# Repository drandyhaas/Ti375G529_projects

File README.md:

# Ti375G529_projects

Test projects for the Efinix Ti375C529 development kit with LPDDR4x memory and FT60X USB3 interface.

## Setup

Make sure to use Zadig to choose the libusb-win32 driver for the Ti dev board interfaces 0 and 1, then it will show up in the programmer.

## Projects

| Directory | Description |
|-----------|-------------|
| [Blink](Blink/) | Simple LED blink example - basic FPGA sanity test |
| [FT601_loopback](FT601_loopback/) | FT60X USB3 loopback test - verify USB communication |
| [LPDDR4](LPDDR4/) | DDR memory test with hardware auto-init and 74+ Gb/s bandwidth verification |
| [LVDS_LPDDR4](LVDS_LPDDR4/) | Digital scope with LVDS inputs, DDR buffering, USB3 readback (Ti375C529) |
| [ti_lpddr4_debug_tools](ti_lpddr4_debug_tools/) | Python tools for DDR calibration and debugging via JTAG |

## Project Details

### [Blink](Blink/)
Minimal LED blink project for verifying FPGA programming and basic I/O.

### [FT601_loopback](FT601_loopback/)
USB3 FT60X interface test. Requires FT60X drivers (v1.3.0.10 recommended) and configuration to 1-channel 245 FIFO mode.

### [LPDDR4](LPDDR4/)
LPDDR4x memory controller test system:
- Hardware auto-initialization on power-up
- LFSR-based memory test with 100% data verification
- 74.36 Gb/s bandwidth (93% efficiency)
- USB3 control interface

### [LVDS_LPDDR4](LVDS_LPDDR4/)
High-speed data acquisition system for Ti375C529:
- 4-channel 10-bit LVDS input at 750 MHz
- LPDDR4 waveform buffer (81+ Gb/s)
- Configurable triggering and downsampling
- USB3 readout (~280 MB/s)
- Command processor with 8-byte protocol

### [ti_lpddr4_debug_tools](ti_lpddr4_debug_tools/)
Python-based DDR debugging and calibration tools:
- JTAG interface for register access
- DDR initialization and training
- Timing scan and calibration
- Gate leveling and read leveling

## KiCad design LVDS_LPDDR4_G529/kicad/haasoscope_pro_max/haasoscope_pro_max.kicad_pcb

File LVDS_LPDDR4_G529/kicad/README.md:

# KiCad Schematic Symbols for Haasoscope Pro Max

This directory contains KiCad schematic symbols and generators for the Haasoscope Pro Max FPGA board.

## Schematic and Board

- [Schematic PDF](haasoscope_pro_max/schematic.pdf)
- [Board Layout](haasoscope_pro_max/board.png)

## Generated Symbols

### Ti90G529_Functions.kicad_sym

Multi-unit FPGA symbol for the Efinix Ti90G529, organized by peripheral interface for easy schematic wiring:

| Unit | Name | Pin Side | Connects To |
|------|------|----------|-------------|
| 1 | FT601 Interface | LEFT | FT601Q USB3 FIFO |
| 2 | ADC 1/2 LVDS Data | RIGHT | ADC12DL500ACF (channels 1-2) |
| 3 | ADC 3/4 LVDS Data | RIGHT | ADC12DL500ACF (channels 3-4) |
| 4 | ADC LVDS Clocks | RIGHT | ADC clock outputs |
| 5 | DDR4 Interface | LEFT (data), RIGHT (control) | MT53D512M16D1DS LPDDR4 |
| 6 | Misc I/O | LEFT (inputs), RIGHT (outputs/SPI) | LEDs, buttons, SPI, etc. |
| 7 | CONFIG/JTAG | LEFT | Programming interface |
| 8 | VCC Power | LEFT and RIGHT | Power supplies |
| 9 | GND | LEFT and RIGHT | Ground |
| 10 | Unassigned GPIO | LEFT | Unused GPIO pins |

### Aligned_Peripheral_Symbols.kicad_sym

Peripheral chip symbols with pins arranged to align with the Ti90G529_Functions symbol:

- **FT601Q_Aligned** - USB3 FIFO, FIFO interface on RIGHT to connect to FPGA on LEFT
- **ADC12DL500ACF_Aligned** - Dual 12-bit ADC, LVDS outputs on LEFT to connect to FPGA on RIGHT
- **MT53D512M16D1DS_Aligned** - LPDDR4 memory, data on RIGHT, control/address on LEFT with gaps for dual-channel wiring

## Symbol Generators

### generate_ti90g529_symbol_with_functions.py

Generates `Ti90G529_Functions.kicad_sym` by parsing the Efinity peri.xml to automatically categorize GPIO pins by their assigned function.

### generate_aligned_peripheral_symbols.py

Generates `Aligned_Peripheral_Symbols.kicad_sym` with pin ordering matched to the FPGA symbol for horizontal wire alignment.

### generate_ti90g529_symbol.py

Base symbol generator with FPGA pin definitions imported by the other generators.

## Original Symbol Sources

- `ADC12DL/` - Original ADC12DL500ACF symbol
- `MT53D512M32D2DS-053 WT_D/` - Original MT53 DDR symbol
- `G529.pretty/` - Footprint library

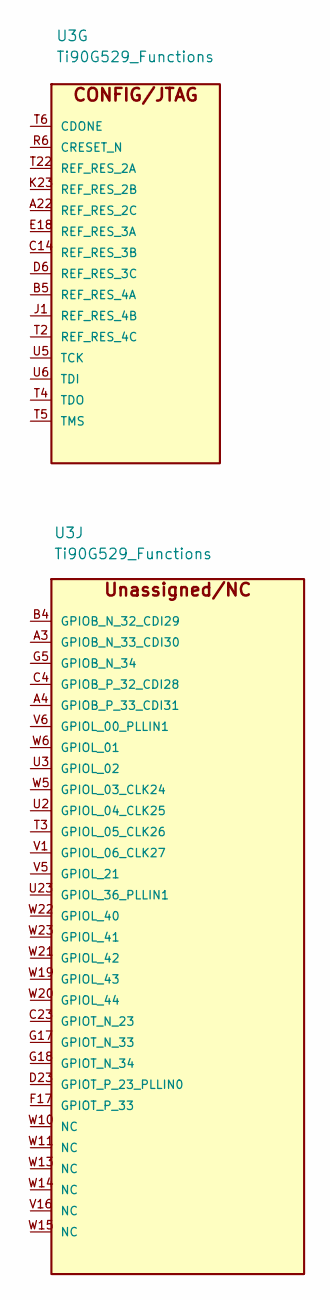
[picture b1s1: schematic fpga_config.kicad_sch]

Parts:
U3: Ti90G529_Functions; BGA-529_23x23_19.0x19.0mm

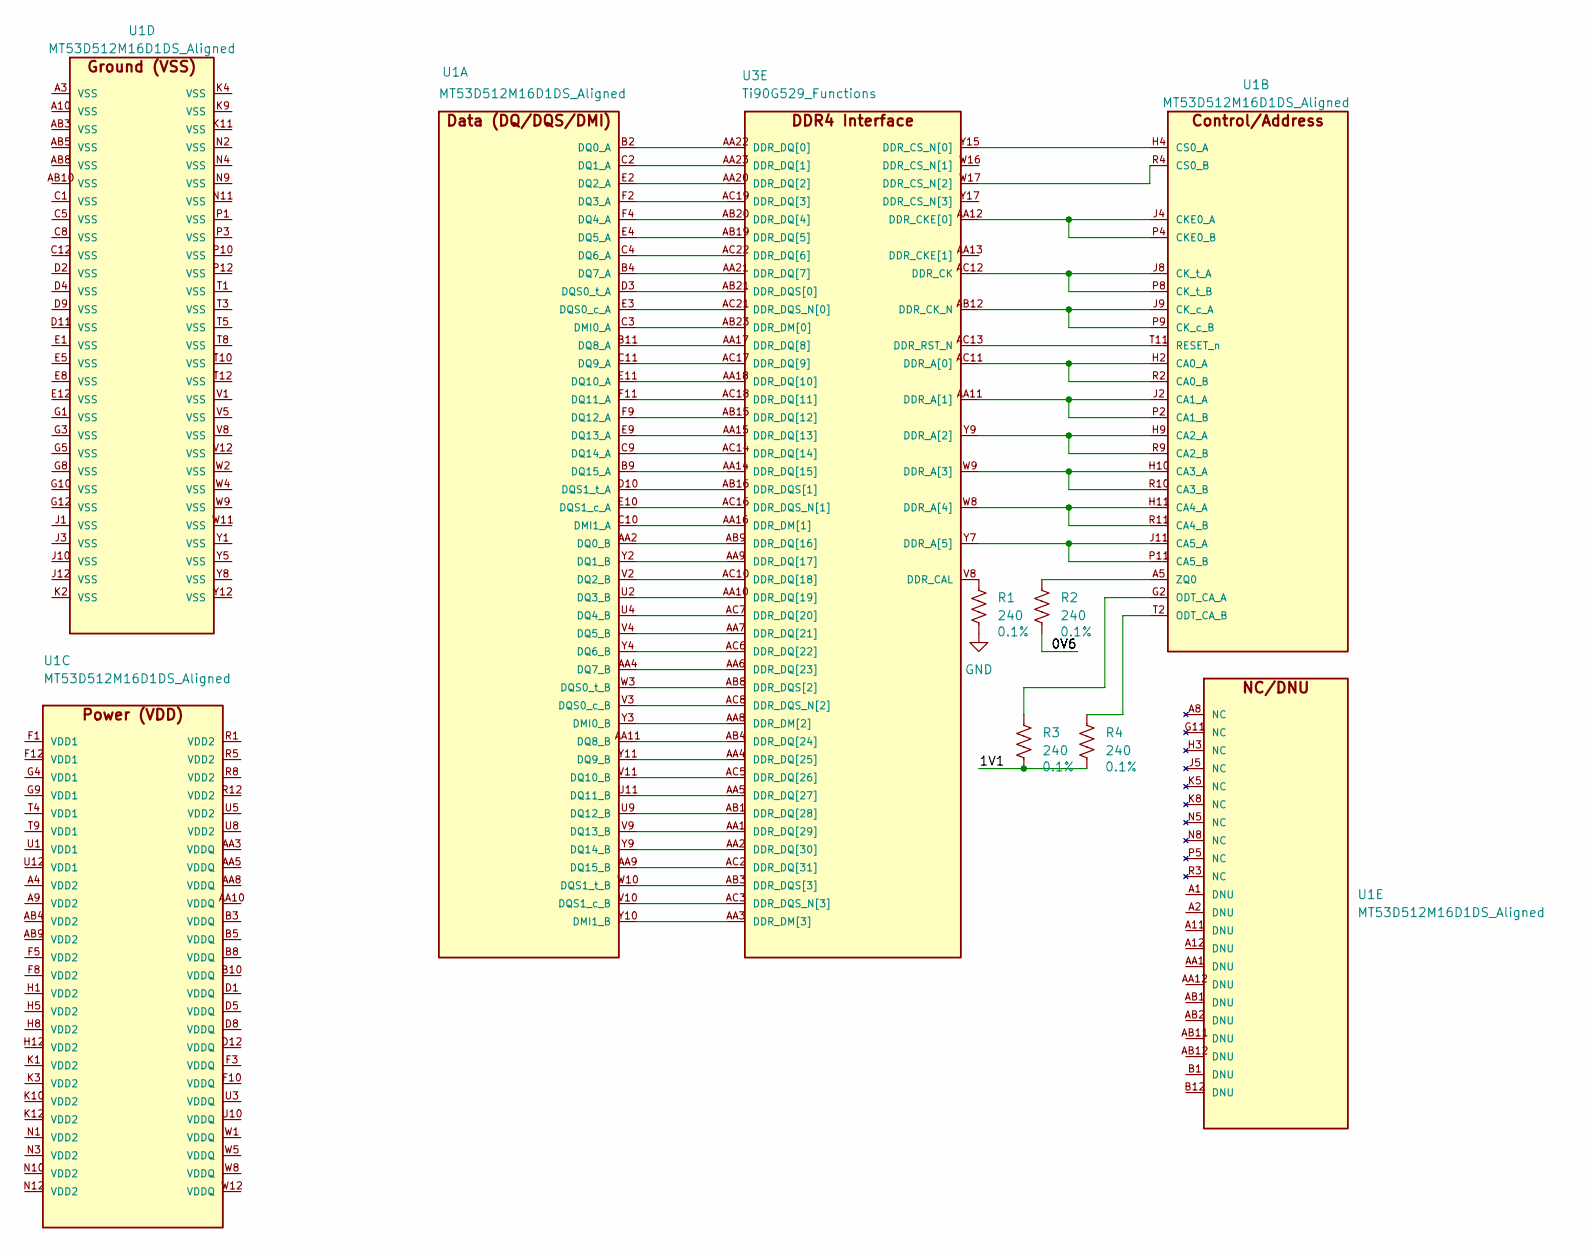
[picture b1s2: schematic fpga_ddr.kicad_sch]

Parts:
R1, R2, R3, R4: 240; R_0402_1005Metric; Tolerance 0.1%
U1: MT53D512M16D1DS_Aligned; IC_MT53D512M16D1DS-046_WT_D
U3: Ti90G529_Functions; BGA-529_23x23_19.0x19.0mm

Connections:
/fpga_ddr/1V1: R3.2, R4.2
GND: R1.2
unnamed: U1.C3 (DMI0_A), U3.AB23 (DDR_DM[0])
unnamed: U1.Y3 (DMI0_B), U3.AA8 (DDR_DM[2])
unnamed: U1.C10 (DMI1_A), U3.AA16 (DDR_DM[1])
unnamed: U1.Y10 (DMI1_B), U3.AA3 (DDR_DM[3])
unnamed: U1.B2 (DQ0_A), U3.AA22 (DDR_DQ[0])
unnamed: U1.AA2 (DQ0_B), U3.AB9 (DDR_DQ[16])
unnamed: U1.C2 (DQ1_A), U3.AA23 (DDR_DQ[1])
unnamed: U1.Y2 (DQ1_B), U3.AA9 (DDR_DQ[17])
unnamed: U1.E2 (DQ2_A), U3.AA20 (DDR_DQ[2])
unnamed: U1.V2 (DQ2_B), U3.AC10 (DDR_DQ[18])
unnamed: U1.F2 (DQ3_A), U3.AC19 (DDR_DQ[3])
unnamed: U1.U2 (DQ3_B), U3.AA10 (DDR_DQ[19])
unnamed: U1.F4 (DQ4_A), U3.AB20 (DDR_DQ[4])
unnamed: U1.U4 (DQ4_B), U3.AC7 (DDR_DQ[20])
unnamed: U1.E4 (DQ5_A), U3.AB19 (DDR_DQ[5])
unnamed: U1.V4 (DQ5_B), U3.AA7 (DDR_DQ[21])
unnamed: U1.C4 (DQ6_A), U3.AC22 (DDR_DQ[6])
unnamed: U1.Y4 (DQ6_B), U3.AC6 (DDR_DQ[22])
unnamed: U1.B4 (DQ7_A), U3.AA21 (DDR_DQ[7])
unnamed: U1.AA4 (DQ7_B), U3.AA6 (DDR_DQ[23])
unnamed: U1.B11 (DQ8_A), U3.AA17 (DDR_DQ[8])
unnamed: U1.AA11 (DQ8_B), U3.AB4 (DDR_DQ[24])
unnamed: U1.C11 (DQ9_A), U3.AC17 (DDR_DQ[9])
unnamed: U1.Y11 (DQ9_B), U3.AA4 (DDR_DQ[25])
unnamed: U1.E11 (DQ10_A), U3.AA18 (DDR_DQ[10])
unnamed: U1.V11 (DQ10_B), U3.AC5 (DDR_DQ[26])
unnamed: U1.F11 (DQ11_A), U3.AC18 (DDR_DQ[11])
unnamed: U1.U11 (DQ11_B), U3.AA5 (DDR_DQ[27])
unnamed: U1.F9 (DQ12_A), U3.AB15 (DDR_DQ[12])
unnamed: U1.U9 (DQ12_B), U3.AB1 (DDR_DQ[28])
unnamed: U1.E9 (DQ13_A), U3.AA15 (DDR_DQ[13])
unnamed: U1.V9 (DQ13_B), U3.AA1 (DDR_DQ[29])
unnamed: U1.C9 (DQ14_A), U3.AC14 (DDR_DQ[14])
unnamed: U1.Y9 (DQ14_B), U3.AA2 (DDR_DQ[30])
unnamed: U1.B9 (DQ15_A), U3.AA14 (DDR_DQ[15])
unnamed: U1.AA9 (DQ15_B), U3.AC2 (DDR_DQ[31])
unnamed: U1.E3 (DQS0_c_A), U3.AC21 (DDR_DQS_N[0])
unnamed: U1.V3 (DQS0_c_B), U3.AC8 (DDR_DQS_N[2])
unnamed: U1.D3 (DQS0_t_A), U3.AB21 (DDR_DQS[0])
unnamed: U1.W3 (DQS0_t_B), U3.AB8 (DDR_DQS[2])
unnamed: U1.E10 (DQS1_c_A), U3.AC16 (DDR_DQS_N[1])
unnamed: U1.V10 (DQS1_c_B), U3.AC3 (DDR_DQS_N[3])
unnamed: U1.D10 (DQS1_t_A), U3.AB16 (DDR_DQS[1])
unnamed: U1.W10 (DQS1_t_B), U3.AB3 (DDR_DQS[3])
unnamed: U1.H2 (CA0_A), U1.R2 (CA0_B), U3.AC11 (DDR_A[0])
unnamed: U1.J2 (CA1_A), U1.P2 (CA1_B), U3.AA11 (DDR_A[1])
unnamed: U1.H9 (CA2_A), U1.R9 (CA2_B), U3.Y9 (DDR_A[2])
unnamed: U1.H10 (CA3_A), U1.R10 (CA3_B), U3.W9 (DDR_A[3])
unnamed: U1.H11 (CA4_A), U1.R11 (CA4_B), U3.W8 (DDR_A[4])
unnamed: U1.J11 (CA5_A), U1.P11 (CA5_B), U3.Y7 (DDR_A[5])
unnamed: U1.J4 (CKE0_A), U1.P4 (CKE0_B), U3.AA12 (DDR_CKE[0])
unnamed: U1.J9 (CK_c_A), U1.P9 (CK_c_B), U3.AB12 (DDR_CK_N)
unnamed: U1.J8 (CK_t_A), U1.P8 (CK_t_B), U3.AC12 (DDR_CK)
unnamed: U1.H4 (CS0_A), U3.Y15 (DDR_CS_N[0])
unnamed: U1.R4 (CS0_B), U3.W17 (DDR_CS_N[2])
unnamed: R3.1, U1.G2 (ODT_CA_A)
unnamed: R4.1, U1.T2 (ODT_CA_B)
unnamed: U1.T11 (RESET_n), U3.AC13 (DDR_RST_N)
unnamed: R2.1, U1.A5 (ZQ0)
unnamed: R1.1, U3.V8 (DDR_CAL)

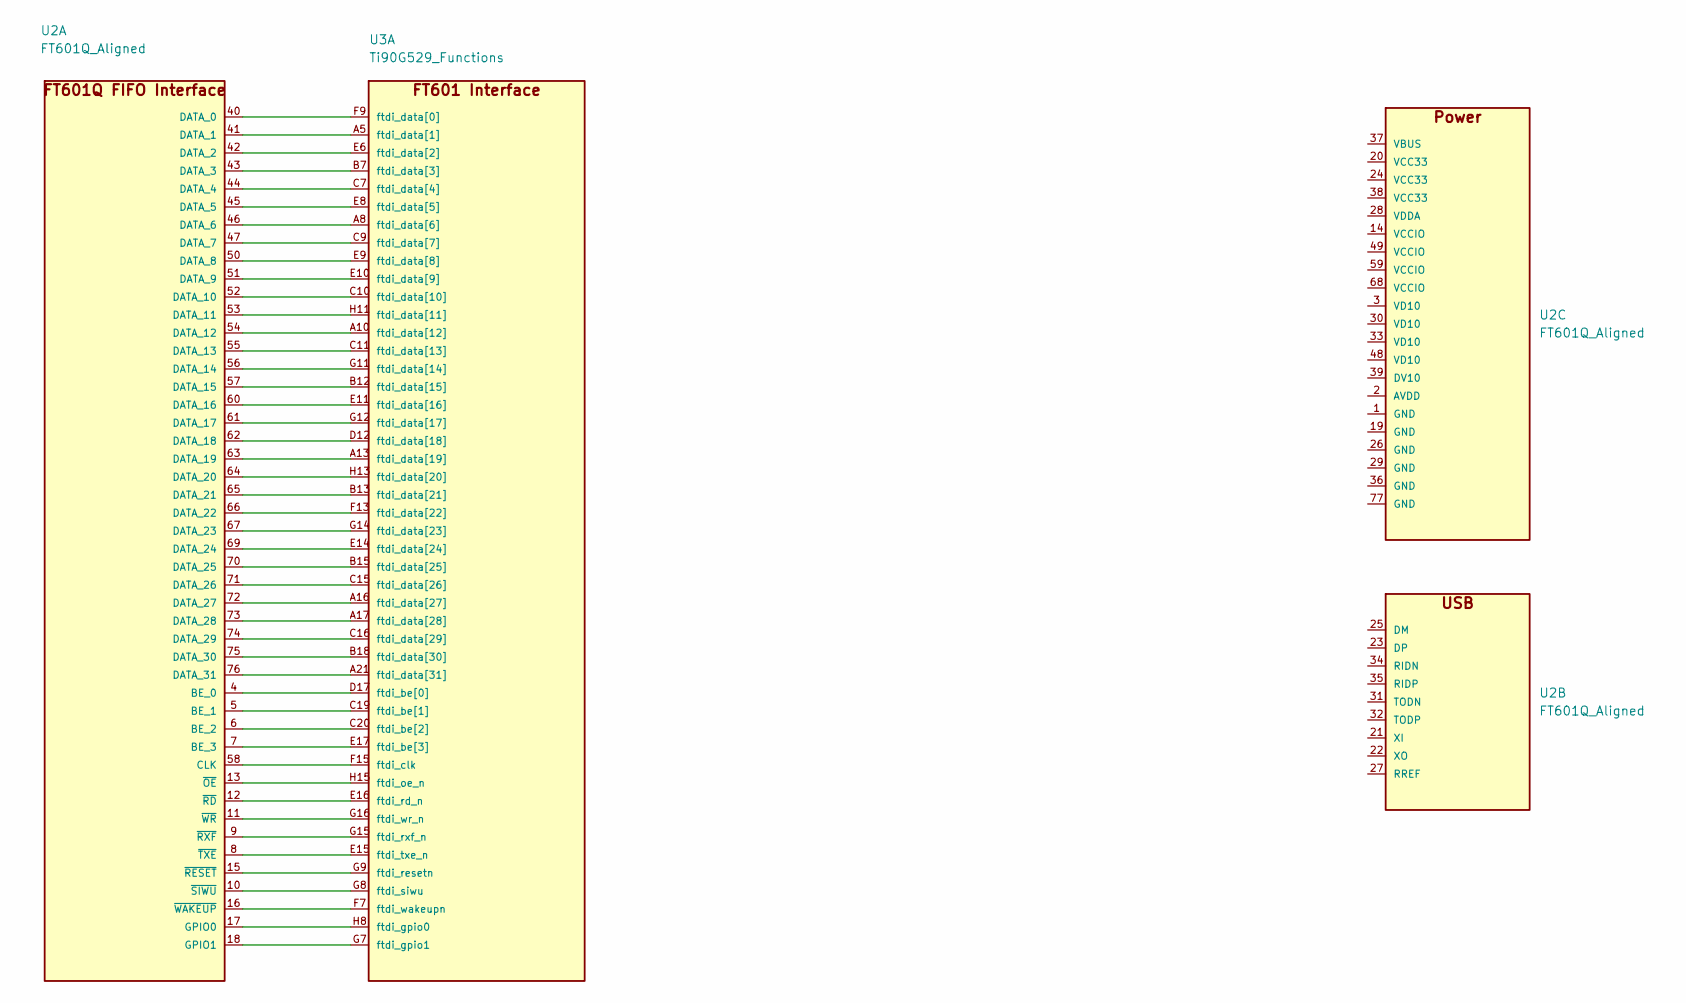
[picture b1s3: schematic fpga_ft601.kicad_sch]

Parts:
U2: FT601Q_Aligned; QFN-76-1EP_9x9mm_P0.4mm_EP5.81x6.31mm
U3: Ti90G529_Functions; BGA-529_23x23_19.0x19.0mm

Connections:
unnamed: U2.4 (BE_0), U3.D17 (ftdi_be[0])
unnamed: U2.5 (BE_1), U3.C19 (ftdi_be[1])
unnamed: U2.6 (BE_2), U3.C20 (ftdi_be[2])
unnamed: U2.7 (BE_3), U3.E17 (ftdi_be[3])
unnamed: U2.58 (CLK), U3.F15 (ftdi_clk)
unnamed: U2.40 (DATA_0), U3.F9 (ftdi_data[0])
unnamed: U2.41 (DATA_1), U3.A5 (ftdi_data[1])
unnamed: U2.42 (DATA_2), U3.E6 (ftdi_data[2])
unnamed: U2.43 (DATA_3), U3.B7 (ftdi_data[3])
unnamed: U2.44 (DATA_4), U3.C7 (ftdi_data[4])
unnamed: U2.45 (DATA_5), U3.E8 (ftdi_data[5])
unnamed: U2.46 (DATA_6), U3.A8 (ftdi_data[6])
unnamed: U2.47 (DATA_7), U3.C9 (ftdi_data[7])
unnamed: U2.50 (DATA_8), U3.E9 (ftdi_data[8])
unnamed: U2.51 (DATA_9), U3.E10 (ftdi_data[9])
unnamed: U2.52 (DATA_10), U3.C10 (ftdi_data[10])
unnamed: U2.53 (DATA_11), U3.H11 (ftdi_data[11])
unnamed: U2.54 (DATA_12), U3.A10 (ftdi_data[12])
unnamed: U2.55 (DATA_13), U3.C11 (ftdi_data[13])
unnamed: U2.56 (DATA_14), U3.G11 (ftdi_data[14])
unnamed: U2.57 (DATA_15), U3.B12 (ftdi_data[15])
unnamed: U2.60 (DATA_16), U3.E11 (ftdi_data[16])
unnamed: U2.61 (DATA_17), U3.G12 (ftdi_data[17])
unnamed: U2.62 (DATA_18), U3.D12 (ftdi_data[18])
unnamed: U2.63 (DATA_19), U3.A13 (ftdi_data[19])
unnamed: U2.64 (DATA_20), U3.H13 (ftdi_data[20])
unnamed: U2.65 (DATA_21), U3.B13 (ftdi_data[21])
unnamed: U2.66 (DATA_22), U3.F13 (ftdi_data[22])
unnamed: U2.67 (DATA_23), U3.G14 (ftdi_data[23])
unnamed: U2.69 (DATA_24), U3.E14 (ftdi_data[24])
unnamed: U2.70 (DATA_25), U3.B15 (ftdi_data[25])
unnamed: U2.71 (DATA_26), U3.C15 (ftdi_data[26])
unnamed: U2.72 (DATA_27), U3.A16 (ftdi_data[27])
unnamed: U2.73 (DATA_28), U3.A17 (ftdi_data[28])
unnamed: U2.74 (DATA_29), U3.C16 (ftdi_data[29])
unnamed: U2.75 (DATA_30), U3.B18 (ftdi_data[30])
unnamed: U2.76 (DATA_31), U3.A21 (ftdi_data[31])
unnamed: U2.17 (GPIO0), U3.H8 (ftdi_gpio0)
unnamed: U2.18 (GPIO1), U3.G7 (ftdi_gpio1)
unnamed: U2.13 (~OE), U3.H15 (ftdi_oe_n)
unnamed: U2.12 (~RD), U3.E16 (ftdi_rd_n)
unnamed: U2.15 (~RESET), U3.G9 (ftdi_resetn)
unnamed: U2.9 (~RXF), U3.G15 (ftdi_rxf_n)
unnamed: U2.10 (~SIWU), U3.G8 (ftdi_siwu)
unnamed: U2.8 (~TXE), U3.E15 (ftdi_txe_n)
unnamed: U2.16 (~WAKEUP), U3.F7 (ftdi_wakeupn)
unnamed: U2.11 (~WR), U3.G16 (ftdi_wr_n)

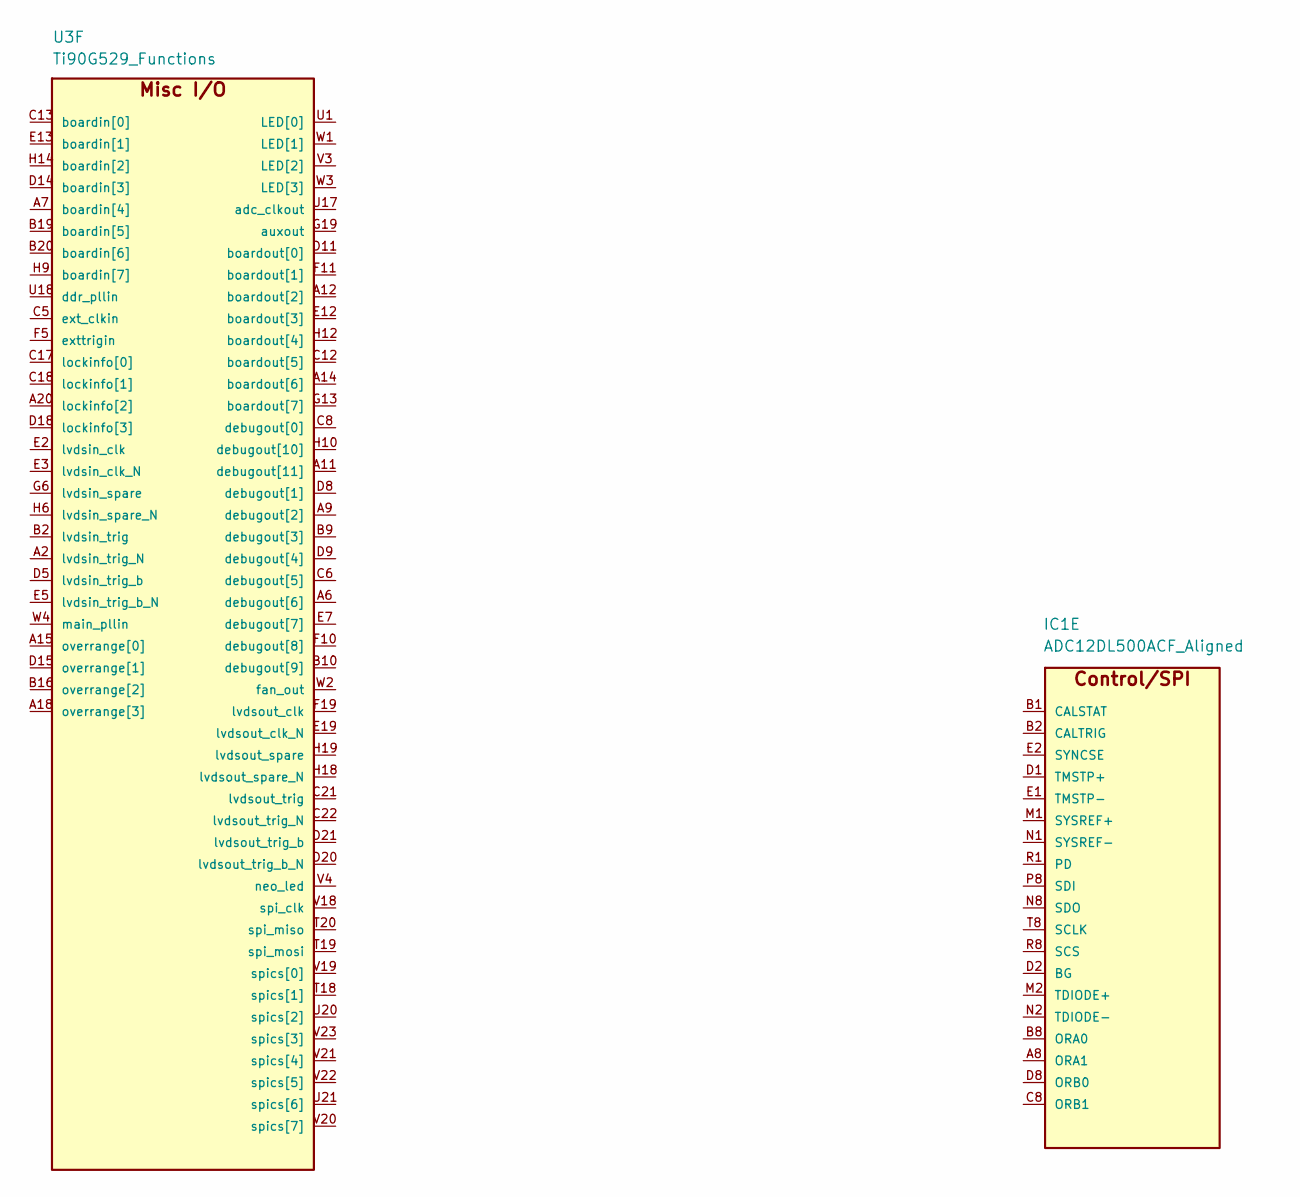
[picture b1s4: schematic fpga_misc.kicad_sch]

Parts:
IC1: ADC12DL500ACF_Aligned; BGA256C100P16X16_1700X1700X331
U3: Ti90G529_Functions; BGA-529_23x23_19.0x19.0mm

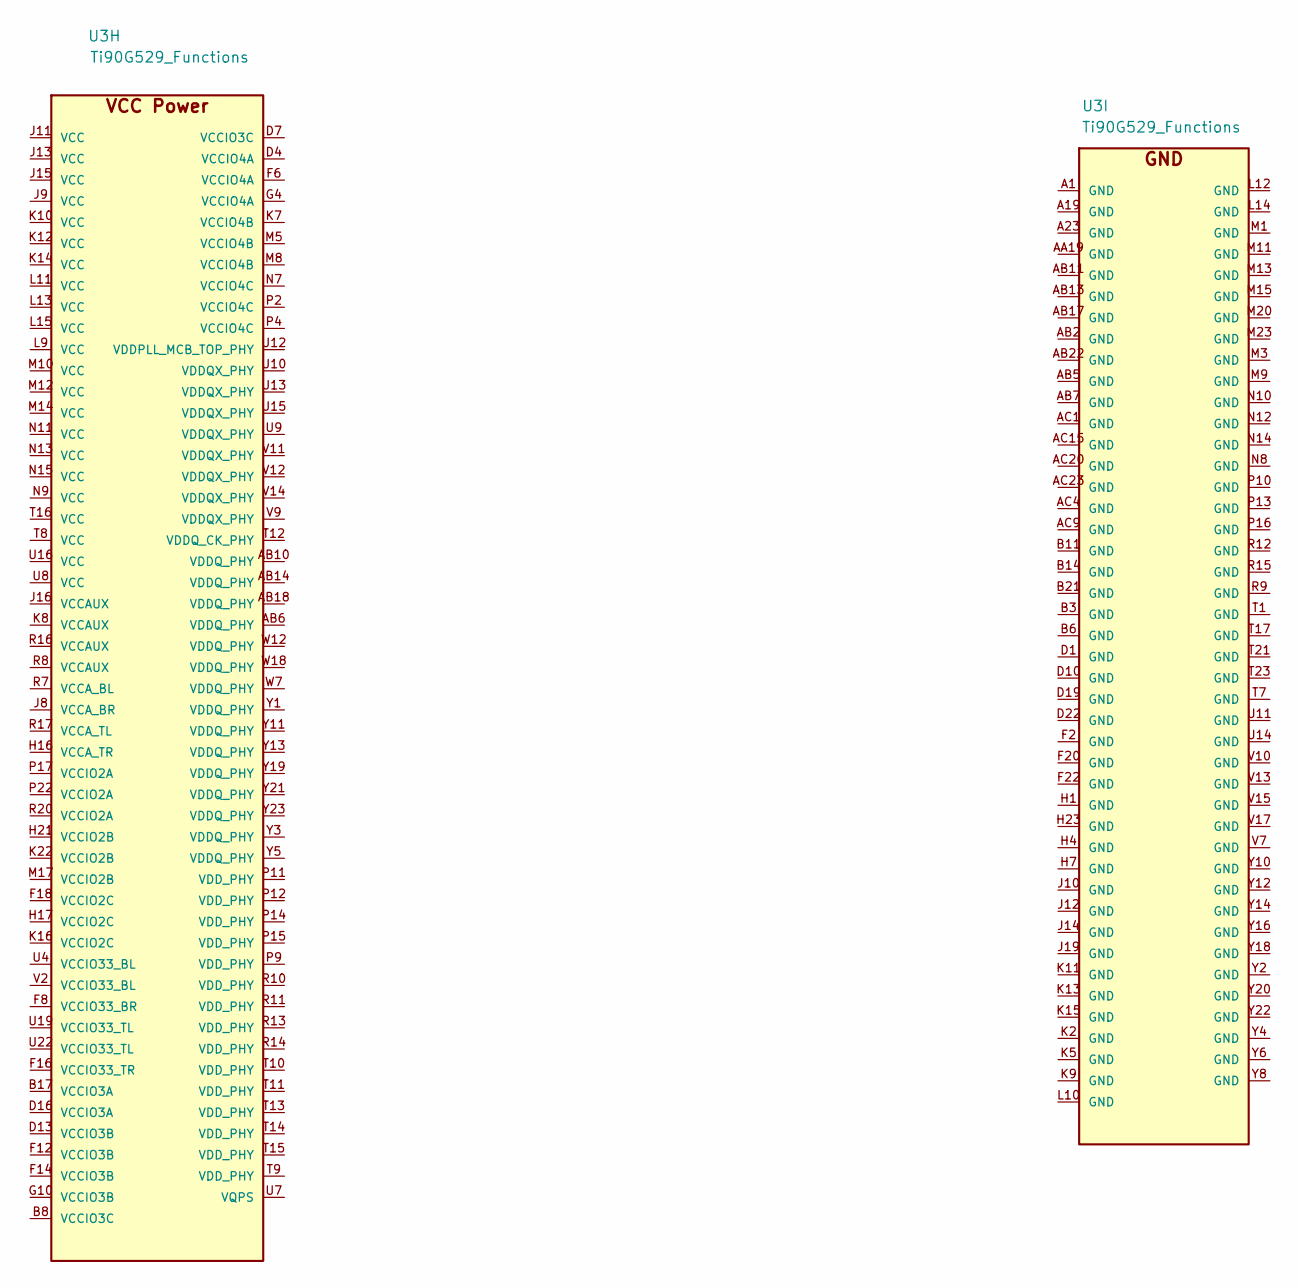
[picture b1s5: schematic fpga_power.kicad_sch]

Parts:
U3: Ti90G529_Functions; BGA-529_23x23_19.0x19.0mm

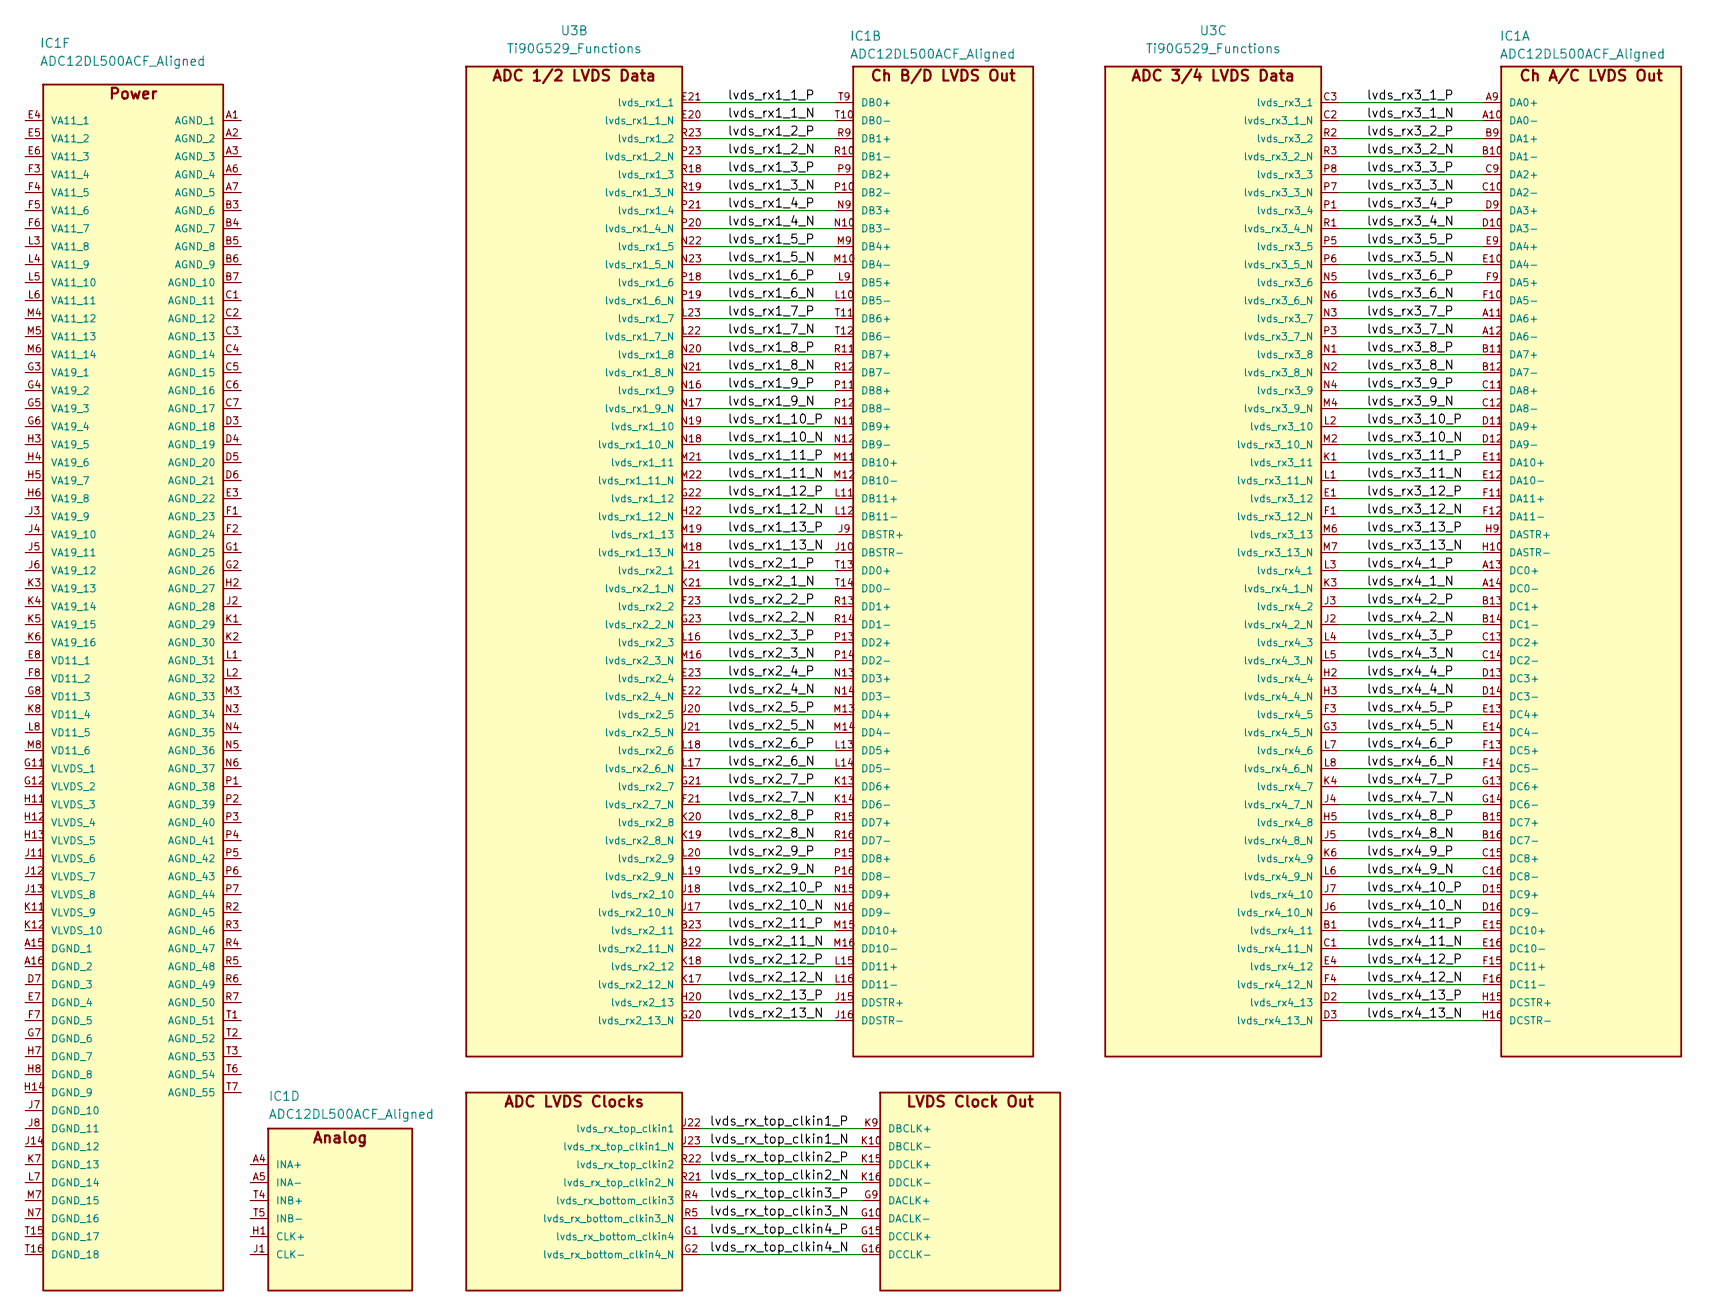
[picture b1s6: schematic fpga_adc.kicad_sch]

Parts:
IC1: ADC12DL500ACF_Aligned; BGA256C100P16X16_1700X1700X331
U3: Ti90G529_Functions; BGA-529_23x23_19.0x19.0mm

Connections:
/fpga_adc/lvds_rx1_1_N: IC1.T10 (DB0-), U3.E20 (lvds_rx1_1_N)
/fpga_adc/lvds_rx1_1_P: IC1.T9 (DB0+), U3.E21 (lvds_rx1_1)
/fpga_adc/lvds_rx1_2_N: IC1.R10 (DB1-), U3.P23 (lvds_rx1_2_N)
/fpga_adc/lvds_rx1_2_P: IC1.R9 (DB1+), U3.R23 (lvds_rx1_2)
/fpga_adc/lvds_rx1_3_N: IC1.P10 (DB2-), U3.R19 (lvds_rx1_3_N)
/fpga_adc/lvds_rx1_3_P: IC1.P9 (DB2+), U3.R18 (lvds_rx1_3)
/fpga_adc/lvds_rx1_4_N: IC1.N10 (DB3-), U3.P20 (lvds_rx1_4_N)
/fpga_adc/lvds_rx1_4_P: IC1.N9 (DB3+), U3.P21 (lvds_rx1_4)
/fpga_adc/lvds_rx1_5_N: IC1.M10 (DB4-), U3.N23 (lvds_rx1_5_N)
/fpga_adc/lvds_rx1_5_P: IC1.M9 (DB4+), U3.N22 (lvds_rx1_5)
/fpga_adc/lvds_rx1_6_N: IC1.L10 (DB5-), U3.P19 (lvds_rx1_6_N)
/fpga_adc/lvds_rx1_6_P: IC1.L9 (DB5+), U3.P18 (lvds_rx1_6)
/fpga_adc/lvds_rx1_7_N: IC1.T12 (DB6-), U3.L22 (lvds_rx1_7_N)
/fpga_adc/lvds_rx1_7_P: IC1.T11 (DB6+), U3.L23 (lvds_rx1_7)
/fpga_adc/lvds_rx1_8_N: IC1.R12 (DB7-), U3.N21 (lvds_rx1_8_N)
/fpga_adc/lvds_rx1_8_P: IC1.R11 (DB7+), U3.N20 (lvds_rx1_8)
/fpga_adc/lvds_rx1_9_N: IC1.P12 (DB8-), U3.N17 (lvds_rx1_9_N)
/fpga_adc/lvds_rx1_9_P: IC1.P11 (DB8+), U3.N16 (lvds_rx1_9)
/fpga_adc/lvds_rx1_10_N: IC1.N12 (DB9-), U3.N18 (lvds_rx1_10_N)
/fpga_adc/lvds_rx1_10_P: IC1.N11 (DB9+), U3.N19 (lvds_rx1_10)
/fpga_adc/lvds_rx1_11_N: IC1.M12 (DB10-), U3.M22 (lvds_rx1_11_N)
/fpga_adc/lvds_rx1_11_P: IC1.M11 (DB10+), U3.M21 (lvds_rx1_11)
/fpga_adc/lvds_rx1_12_N: IC1.L12 (DB11-), U3.H22 (lvds_rx1_12_N)
/fpga_adc/lvds_rx1_12_P: IC1.L11 (DB11+), U3.G22 (lvds_rx1_12)
/fpga_adc/lvds_rx1_13_N: IC1.J10 (DBSTR-), U3.M18 (lvds_rx1_13_N)
/fpga_adc/lvds_rx1_13_P: IC1.J9 (DBSTR+), U3.M19 (lvds_rx1_13)
/fpga_adc/lvds_rx2_1_N: IC1.T14 (DD0-), U3.K21 (lvds_rx2_1_N)
/fpga_adc/lvds_rx2_1_P: IC1.T13 (DD0+), U3.L21 (lvds_rx2_1)
/fpga_adc/lvds_rx2_2_N: IC1.R14 (DD1-), U3.G23 (lvds_rx2_2_N)
/fpga_adc/lvds_rx2_2_P: IC1.R13 (DD1+), U3.F23 (lvds_rx2_2)
/fpga_adc/lvds_rx2_3_N: IC1.P14 (DD2-), U3.M16 (lvds_rx2_3_N)
/fpga_adc/lvds_rx2_3_P: IC1.P13 (DD2+), U3.L16 (lvds_rx2_3)
/fpga_adc/lvds_rx2_4_N: IC1.N14 (DD3-), U3.E22 (lvds_rx2_4_N)
/fpga_adc/lvds_rx2_4_P: IC1.N13 (DD3+), U3.E23 (lvds_rx2_4)
/fpga_adc/lvds_rx2_5_N: IC1.M14 (DD4-), U3.J21 (lvds_rx2_5_N)
/fpga_adc/lvds_rx2_5_P: IC1.M13 (DD4+), U3.J20 (lvds_rx2_5)
/fpga_adc/lvds_rx2_6_N: IC1.L14 (DD5-), U3.L17 (lvds_rx2_6_N)
/fpga_adc/lvds_rx2_6_P: IC1.L13 (DD5+), U3.L18 (lvds_rx2_6)
/fpga_adc/lvds_rx2_7_N: IC1.K14 (DD6-), U3.F21 (lvds_rx2_7_N)
/fpga_adc/lvds_rx2_7_P: IC1.K13 (DD6+), U3.G21 (lvds_rx2_7)
/fpga_adc/lvds_rx2_8_N: IC1.R16 (DD7-), U3.K19 (lvds_rx2_8_N)
/fpga_adc/lvds_rx2_8_P: IC1.R15 (DD7+), U3.K20 (lvds_rx2_8)
/fpga_adc/lvds_rx2_9_N: IC1.P16 (DD8-), U3.L19 (lvds_rx2_9_N)
/fpga_adc/lvds_rx2_9_P: IC1.P15 (DD8+), U3.L20 (lvds_rx2_9)
/fpga_adc/lvds_rx2_10_N: IC1.N16 (DD9-), U3.J17 (lvds_rx2_10_N)
/fpga_adc/lvds_rx2_10_P: IC1.N15 (DD9+), U3.J18 (lvds_rx2_10)
/fpga_adc/lvds_rx2_11_N: IC1.M16 (DD10-), U3.B22 (lvds_rx2_11_N)
/fpga_adc/lvds_rx2_11_P: IC1.M15 (DD10+), U3.B23 (lvds_rx2_11)
/fpga_adc/lvds_rx2_12_N: IC1.L16 (DD11-), U3.K17 (lvds_rx2_12_N)
/fpga_adc/lvds_rx2_12_P: IC1.L15 (DD11+), U3.K18 (lvds_rx2_12)
/fpga_adc/lvds_rx2_13_N: IC1.J16 (DDSTR-), U3.G20 (lvds_rx2_13_N)
/fpga_adc/lvds_rx2_13_P: IC1.J15 (DDSTR+), U3.H20 (lvds_rx2_13)
/fpga_adc/lvds_rx3_1_N: IC1.A10 (DA0-), U3.C2 (lvds_rx3_1_N)
/fpga_adc/lvds_rx3_1_P: IC1.A9 (DA0+), U3.C3 (lvds_rx3_1)
/fpga_adc/lvds_rx3_2_N: IC1.B10 (DA1-), U3.R3 (lvds_rx3_2_N)
/fpga_adc/lvds_rx3_2_P: IC1.B9 (DA1+), U3.R2 (lvds_rx3_2)
/fpga_adc/lvds_rx3_3_N: IC1.C10 (DA2-), U3.P7 (lvds_rx3_3_N)
/fpga_adc/lvds_rx3_3_P: IC1.C9 (DA2+), U3.P8 (lvds_rx3_3)
/fpga_adc/lvds_rx3_4_N: IC1.D10 (DA3-), U3.R1 (lvds_rx3_4_N)
/fpga_adc/lvds_rx3_4_P: IC1.D9 (DA3+), U3.P1 (lvds_rx3_4)
/fpga_adc/lvds_rx3_5_N: IC1.E10 (DA4-), U3.P6 (lvds_rx3_5_N)
/fpga_adc/lvds_rx3_5_P: IC1.E9 (DA4+), U3.P5 (lvds_rx3_5)
/fpga_adc/lvds_rx3_6_N: IC1.F10 (DA5-), U3.N6 (lvds_rx3_6_N)
/fpga_adc/lvds_rx3_6_P: IC1.F9 (DA5+), U3.N5 (lvds_rx3_6)
/fpga_adc/lvds_rx3_7_N: IC1.A12 (DA6-), U3.P3 (lvds_rx3_7_N)
/fpga_adc/lvds_rx3_7_P: IC1.A11 (DA6+), U3.N3 (lvds_rx3_7)
/fpga_adc/lvds_rx3_8_N: IC1.B12 (DA7-), U3.N2 (lvds_rx3_8_N)
/fpga_adc/lvds_rx3_8_P: IC1.B11 (DA7+), U3.N1 (lvds_rx3_8)
/fpga_adc/lvds_rx3_9_N: IC1.C12 (DA8-), U3.M4 (lvds_rx3_9_N)
/fpga_adc/lvds_rx3_9_P: IC1.C11 (DA8+), U3.N4 (lvds_rx3_9)
/fpga_adc/lvds_rx3_10_N: IC1.D12 (DA9-), U3.M2 (lvds_rx3_10_N)
/fpga_adc/lvds_rx3_10_P: IC1.D11 (DA9+), U3.L2 (lvds_rx3_10)
/fpga_adc/lvds_rx3_11_N: IC1.E12 (DA10-), U3.L1 (lvds_rx3_11_N)
/fpga_adc/lvds_rx3_11_P: IC1.E11 (DA10+), U3.K1 (lvds_rx3_11)
/fpga_adc/lvds_rx3_12_N: IC1.F12 (DA11-), U3.F1 (lvds_rx3_12_N)
/fpga_adc/lvds_rx3_12_P: IC1.F11 (DA11+), U3.E1 (lvds_rx3_12)
/fpga_adc/lvds_rx3_13_N: IC1.H10 (DASTR-), U3.M7 (lvds_rx3_13_N)
/fpga_adc/lvds_rx3_13_P: IC1.H9 (DASTR+), U3.M6 (lvds_rx3_13)
/fpga_adc/lvds_rx4_1_N: IC1.A14 (DC0-), U3.K3 (lvds_rx4_1_N)
/fpga_adc/lvds_rx4_1_P: IC1.A13 (DC0+), U3.L3 (lvds_rx4_1)
/fpga_adc/lvds_rx4_2_N: IC1.B14 (DC1-), U3.J2 (lvds_rx4_2_N)
/fpga_adc/lvds_rx4_2_P: IC1.B13 (DC1+), U3.J3 (lvds_rx4_2)
/fpga_adc/lvds_rx4_3_N: IC1.C14 (DC2-), U3.L5 (lvds_rx4_3_N)
/fpga_adc/lvds_rx4_3_P: IC1.C13 (DC2+), U3.L4 (lvds_rx4_3)
/fpga_adc/lvds_rx4_4_N: IC1.D14 (DC3-), U3.H3 (lvds_rx4_4_N)
/fpga_adc/lvds_rx4_4_P: IC1.D13 (DC3+), U3.H2 (lvds_rx4_4)
/fpga_adc/lvds_rx4_5_N: IC1.E14 (DC4-), U3.G3 (lvds_rx4_5_N)
/fpga_adc/lvds_rx4_5_P: IC1.E13 (DC4+), U3.F3 (lvds_rx4_5)
/fpga_adc/lvds_rx4_6_N: IC1.F14 (DC5-), U3.L8 (lvds_rx4_6_N)
/fpga_adc/lvds_rx4_6_P: IC1.F13 (DC5+), U3.L7 (lvds_rx4_6)
/fpga_adc/lvds_rx4_7_N: IC1.G14 (DC6-), U3.J4 (lvds_rx4_7_N)
/fpga_adc/lvds_rx4_7_P: IC1.G13 (DC6+), U3.K4 (lvds_rx4_7)
/fpga_adc/lvds_rx4_8_N: IC1.B16 (DC7-), U3.J5 (lvds_rx4_8_N)
/fpga_adc/lvds_rx4_8_P: IC1.B15 (DC7+), U3.H5 (lvds_rx4_8)
/fpga_adc/lvds_rx4_9_N: IC1.C16 (DC8-), U3.L6 (lvds_rx4_9_N)
/fpga_adc/lvds_rx4_9_P: IC1.C15 (DC8+), U3.K6 (lvds_rx4_9)
/fpga_adc/lvds_rx4_10_N: IC1.D16 (DC9-), U3.J6 (lvds_rx4_10_N)
/fpga_adc/lvds_rx4_10_P: IC1.D15 (DC9+), U3.J7 (lvds_rx4_10)
/fpga_adc/lvds_rx4_11_N: IC1.E16 (DC10-), U3.C1 (lvds_rx4_11_N)
/fpga_adc/lvds_rx4_11_P: IC1.E15 (DC10+), U3.B1 (lvds_rx4_11)
/fpga_adc/lvds_rx4_12_N: IC1.F16 (DC11-), U3.F4 (lvds_rx4_12_N)
/fpga_adc/lvds_rx4_12_P: IC1.F15 (DC11+), U3.E4 (lvds_rx4_12)
/fpga_adc/lvds_rx4_13_N: IC1.H16 (DCSTR-), U3.D3 (lvds_rx4_13_N)
/fpga_adc/lvds_rx4_13_P: IC1.H15 (DCSTR+), U3.D2 (lvds_rx4_13)
/fpga_adc/lvds_rx_top_clkin1_N: IC1.K10 (DBCLK-), U3.J23 (lvds_rx_top_clkin1_N)
/fpga_adc/lvds_rx_top_clkin1_P: IC1.K9 (DBCLK+), U3.J22 (lvds_rx_top_clkin1)
/fpga_adc/lvds_rx_top_clkin2_N: IC1.K16 (DDCLK-), U3.R21 (lvds_rx_top_clkin2_N)
/fpga_adc/lvds_rx_top_clkin2_P: IC1.K15 (DDCLK+), U3.R22 (lvds_rx_top_clkin2)
/fpga_adc/lvds_rx_top_clkin3_N: IC1.G10 (DACLK-), U3.R5 (lvds_rx_bottom_clkin3_N)
/fpga_adc/lvds_rx_top_clkin3_P: IC1.G9 (DACLK+), U3.R4 (lvds_rx_bottom_clkin3)
/fpga_adc/lvds_rx_top_clkin4_N: IC1.G16 (DCCLK-), U3.G2 (lvds_rx_bottom_clkin4_N)
/fpga_adc/lvds_rx_top_clkin4_P: IC1.G15 (DCCLK+), U3.G1 (lvds_rx_bottom_clkin4)

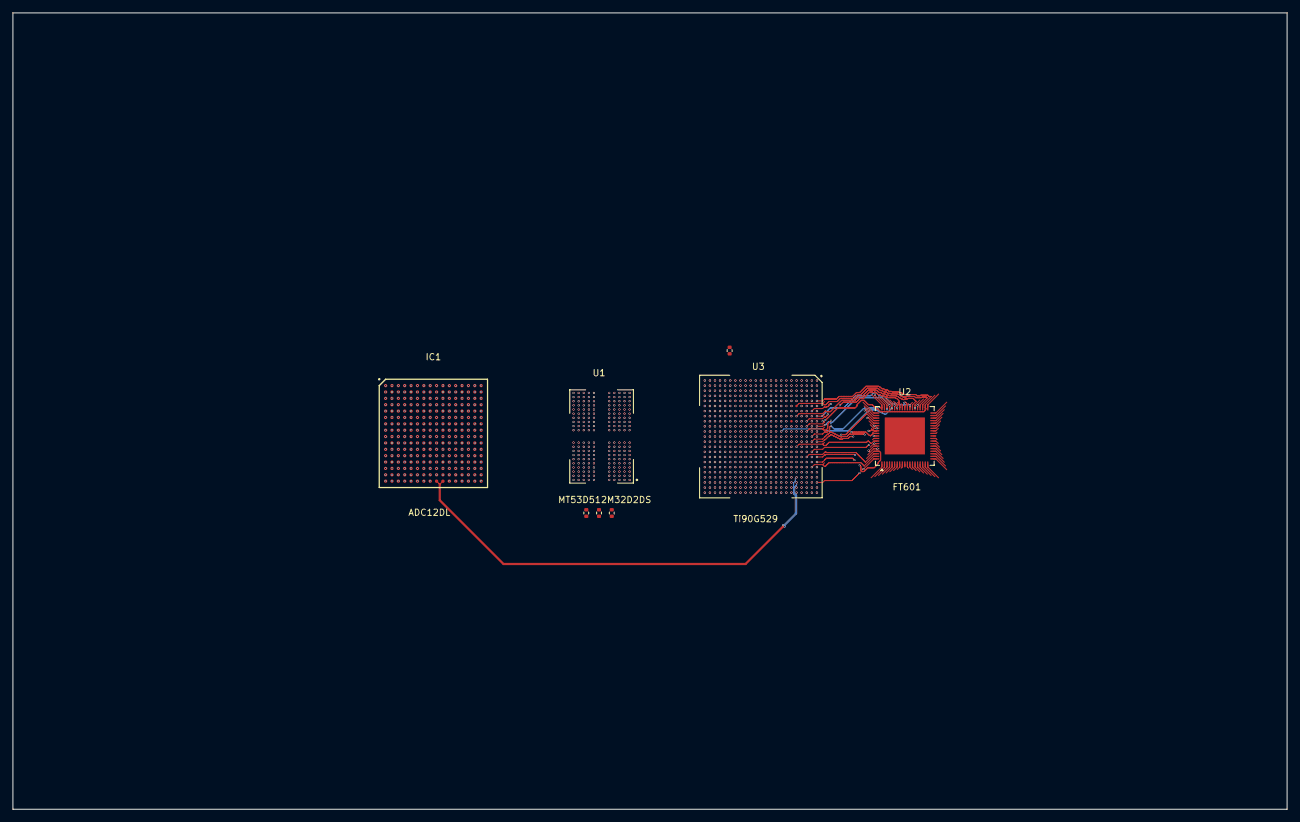
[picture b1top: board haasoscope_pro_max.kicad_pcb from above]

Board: 10 copper layers, 200.0 x 125.0 mm, 8 parts (0 on the bottom side), 220 nets.
